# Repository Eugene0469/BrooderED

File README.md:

# BrooderED
This repo contains all ED of the brooder bora

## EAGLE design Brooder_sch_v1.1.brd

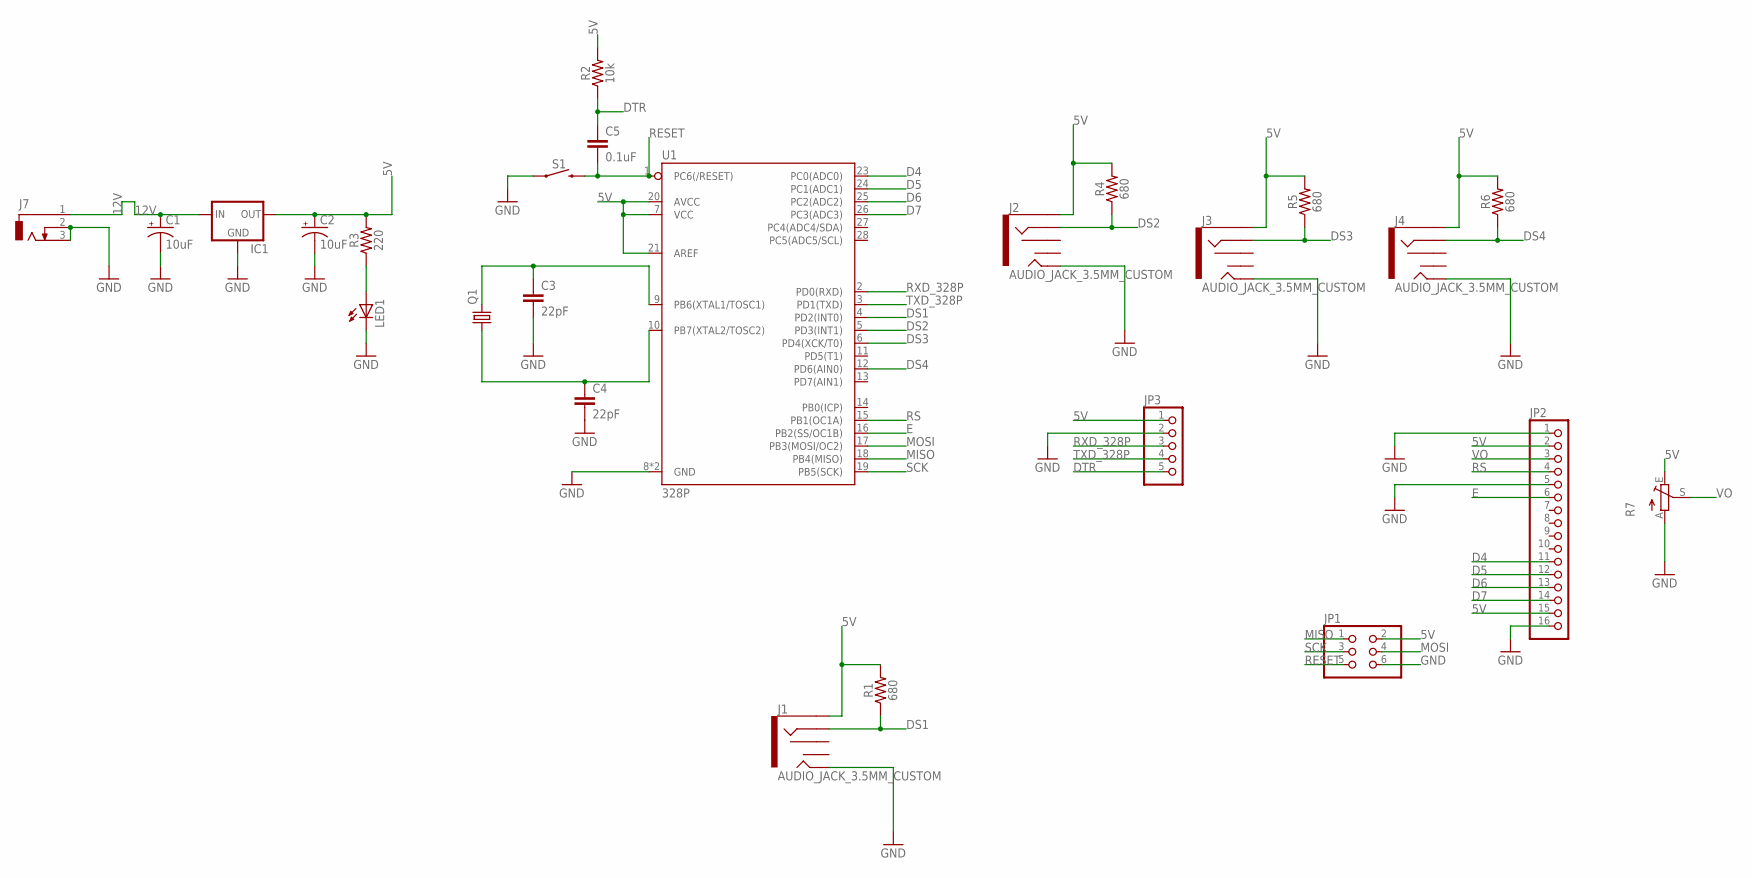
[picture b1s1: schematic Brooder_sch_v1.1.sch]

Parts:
C1, C2: 10uF; CPOL-RADIAL-2.5MM-5MM
C3, C4: 22pF; CAP-PTH-2.54
C5: 0.1uF; CAP-PTH-2.54
IC1: 78XXS
J1, J2, J3, J4: AUDIO_JACK_3.5MM_CUSTOM; AUDIO-JACK_CUSTOM
J7: DCJ0303_CUSTOM
JP1: PINHD-2X3; 2X03
JP2: PINHD-1X16; 1X16
JP3: PINHD-1X5; 1X05
LED1: LED5MM
Q1: CRYSTALHC49S; HC49/S
R1, R4, R5, R6: 680; AXIAL-0.3
R2: 10k; AXIAL-0.3
R3: 220; AXIAL-0.3
R7: TRIM_EU-CT6; CT6
S1: SWITCH; TACTILE_SWITCH_PTH_6.0MM
U1: 328P; DIP28

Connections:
5V: C2.1 (+), IC1.OUT, J1.SLEEVE, J2.SLEEVE, J3.SLEEVE, J4.SLEEVE, JP1.2, JP2.2, JP2.15, JP3.1, R1.P$2 (2), R2.P$2 (2), R3.P$2 (2), R4.P$2 (2), R5.P$2 (2), R6.P$2 (2), R7.E, U1.7 (VCC), U1.20 (AVCC), U1.21 (AREF)
12V: C1.1 (+), IC1.IN, J7.1
D4: JP2.11, U1.23 (PC0(ADC0))
D5: JP2.12, U1.24 (PC1(ADC1))
D6: JP2.13, U1.25 (PC2(ADC2))
D7: JP2.14, U1.26 (PC3(ADC3))
DS1: J1.RING, R1.P$1 (1), U1.4 (PD2(INT0))
DS2: J2.RING, R4.P$1 (1), U1.5 (PD3(INT1))
DS3: J3.RING, R5.P$1 (1), U1.6 (PD4(XCK/T0))
DS4: J4.RING, R6.P$1 (1), U1.12 (PD6(AIN0))
DTR: C5.1, JP3.5, R2.P$1 (1)
E: JP2.6, U1.16 (PB2(SS/OC1B))
GND: C1.2 (-), C2.2 (-), C3.2, C4.2, IC1.GND, J1.TIP, J2.TIP, J3.TIP, J4.TIP, J7.2, J7.3, JP1.6, JP2.1, JP2.5, JP2.16, JP3.2, LED1.K (C), R7.A, S1.1, U1.8 (GND), U1.22 (GND)
MISO: JP1.1, U1.18 (PB4(MISO))
MOSI: JP1.4, U1.17 (PB3(MOSI/OC2))
unnamed: LED1.A, R3.P$1 (1)
unnamed: C4.1, Q1.1, U1.10 (PB7(XTAL2/TOSC2))
unnamed: C3.1, Q1.2, U1.9 (PB6(XTAL1/TOSC1))
RESET: C5.2, JP1.5, S1.3 (2), U1.1 (PC6(/RESET))
RS: JP2.4, U1.15 (PB1(OC1A))
RXD_328P: JP3.3, U1.2 (PD0(RXD))
SCK: JP1.3, U1.19 (PB5(SCK))
TXD_328P: JP3.4, U1.3 (PD1(TXD))
VO: JP2.3, R7.S

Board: 2 copper layers, 25 parts (1 on the bottom side), 24 nets, no tracks yet.

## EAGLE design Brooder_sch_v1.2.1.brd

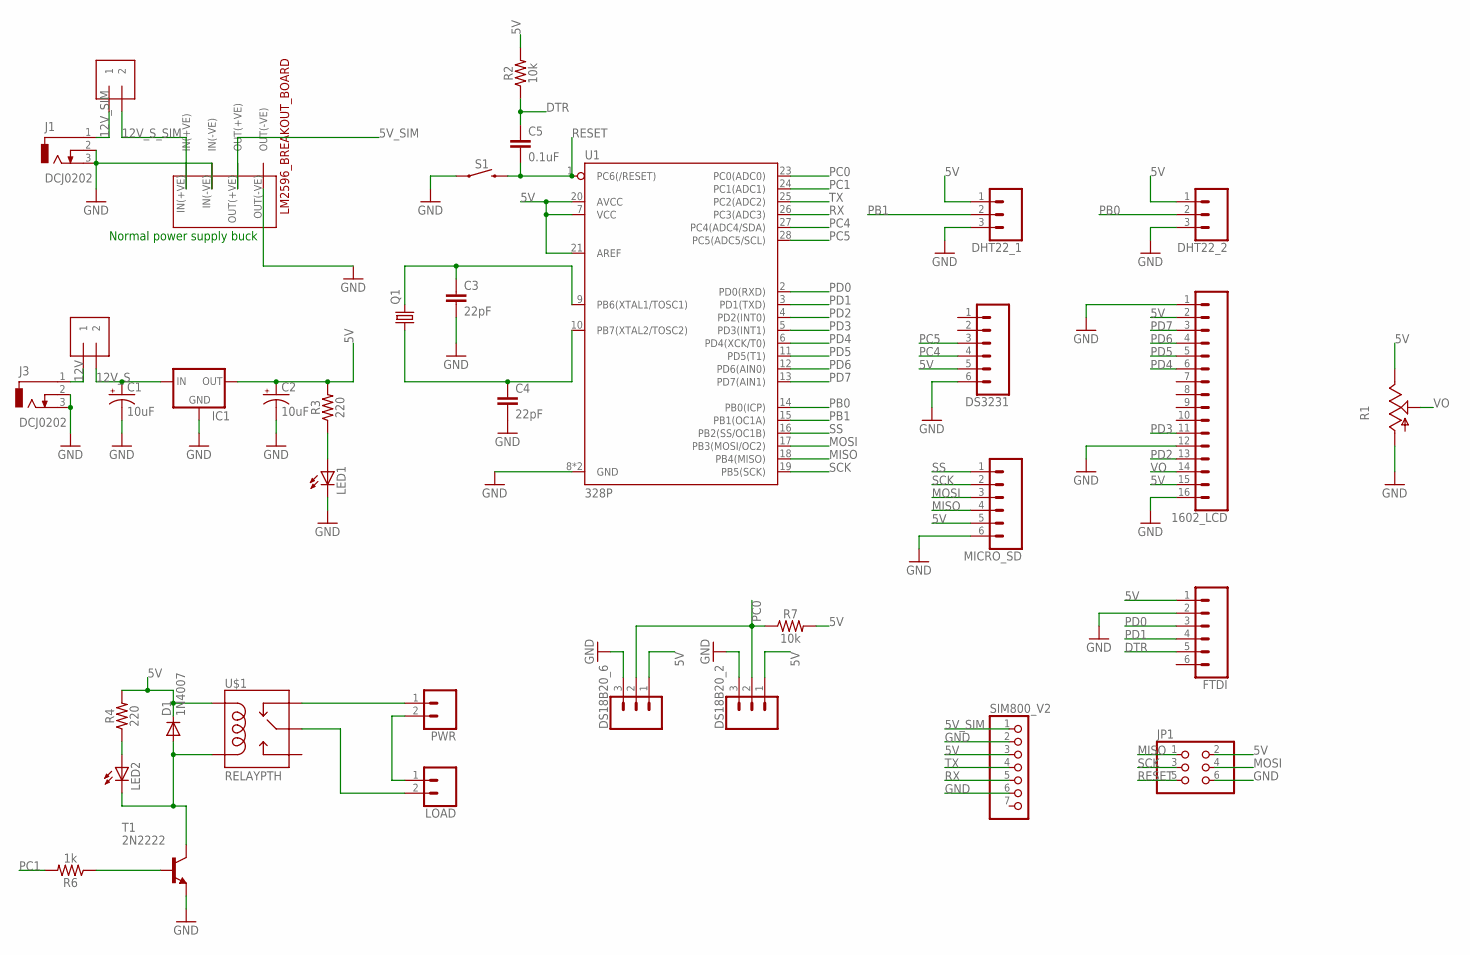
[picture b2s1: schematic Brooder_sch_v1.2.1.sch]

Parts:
1602_LCD: CONN_161X16_NO_SILK; 1X16_NO_SILK
C1, C2: 10uF; CPOL-RADIAL-2.5MM-5MM
C3, C4: 22pF; CAP-PTH-2.54
C5: 0.1uF; CAP-PTH-2.54
D1: 1N4007; DO41-10
DHT22_1: dht22_1; 1X03
DHT22_2: 455-1750-1-ND; 1X03
DS18B20_2, DS18B20_6: 455-1750-1-ND; 1X03
DS3231: CONN_06NO_SILK_FEMALE_PTH; 1X06_NO_SILK
FTDI: CONN_06NO_SILK_FEMALE_PTH; 1X06_NO_SILK
IC1: 78XXS
J1, J3: DCJ0202
J2, J4: 1X2-3.5MM
JP1: PINHD-2X3; 2X03
LED1, LED2: LED5MM
LOAD: CONN_025MM; SCREWTERMINAL-5MM-2
MICRO_SD: CONN_06NO_SILK_FEMALE_PTH; 1X06_NO_SILK
PWR: CONN_025MM; SCREWTERMINAL-5MM-2
Q1: CRYSTALHC49S; HC49/S
R1: TRIM_US-CT6; CT6
R2, R7: 10k; AXIAL-0.3
R3, R4: 220; AXIAL-0.3
R6: 1k; AXIAL-0.3
S1: SWITCH; TACTILE_SWITCH_PTH_6.0MM
SIM800_V2: PINHD-1X7; 1X07
T1: 2N2222; TO92-EBC-OVAL
U1: 328P; DIP28
U$1: RELAYPTH; SRD-05VDC-SL-C
U$2: LM2596_BREAKOUT_BOARDTHROUGH_HOLE; LM2596_BREAKOUTBOARD

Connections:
5V: 1602_LCD.2, 1602_LCD.15, C2.1 (+), D1.C, DHT22_1.1, DHT22_2.1, DS18B20_2.1, DS18B20_6.1, DS3231.5, FTDI.1, IC1.OUT, JP1.2, MICRO_SD.5, R1.E, R2.P$2 (2), R3.P$2 (2), R4.P$2 (2), R7.P$2 (2), SIM800_V2.3, U1.7 (VCC), U1.20 (AVCC), U1.21 (AREF), U$1.COIL1
5V_SIM: SIM800_V2.1, U$2.OUT(+VE)
12V: J3.1, J4.1
12V_S: C1.1 (+), IC1.IN, J4.2
12V_SIM: J1.1, J2.1
12V_S_SIM: J2.2, U$2.IN(+VE)
DTR: C5.1, FTDI.5, R2.P$1 (1)
GND: 1602_LCD.1, 1602_LCD.12, 1602_LCD.16, C1.2 (-), C2.2 (-), C3.2, C4.2, DHT22_1.3, DHT22_2.3, DS18B20_2.3, DS18B20_6.3, DS3231.6, FTDI.2, IC1.GND, J1.2, J1.3, J3.2, J3.3, JP1.6, LED1.K (C), MICRO_SD.6, R1.A, S1.1, SIM800_V2.2, SIM800_V2.6, T1.E, U1.8 (GND), U1.22 (GND), U$2.IN(-VE), U$2.OUT(-VE)
MISO: JP1.1, MICRO_SD.4, U1.18 (PB4(MISO))
MOSI: JP1.4, MICRO_SD.3, U1.17 (PB3(MOSI/OC2))
unnamed: LOAD.2, U$1.SWCOMMON
unnamed: LED1.A, R3.P$1 (1)
unnamed: LOAD.1, PWR.2
unnamed: C4.1, Q1.1, U1.10 (PB7(XTAL2/TOSC2))
unnamed: D1.A, LED2.K (C), T1.C, U$1.COIL0
unnamed: LED2.A, R4.P$1 (1)
unnamed: C3.1, Q1.2, U1.9 (PB6(XTAL1/TOSC1))
unnamed: R6.P$1 (1), T1.B
unnamed: PWR.1, U$1.SWCLOSED (SWCLOSE)
PB0: DHT22_2.2, U1.14 (PB0(ICP))
PB1: DHT22_1.2, U1.15 (PB1(OC1A))
PC0: DS18B20_2.2, DS18B20_6.2, R7.P$1 (1), U1.23 (PC0(ADC0))
PC1: R6.P$2 (2), U1.24 (PC1(ADC1))
PC4: DS3231.4, U1.27 (PC4(ADC4/SDA))
PC5: DS3231.3, U1.28 (PC5(ADC5/SCL))
PD0: FTDI.3, U1.2 (PD0(RXD))
PD1: FTDI.4, U1.3 (PD1(TXD))
PD2: 1602_LCD.13, U1.4 (PD2(INT0))
PD3: 1602_LCD.11, U1.5 (PD3(INT1))
PD4: 1602_LCD.6, U1.6 (PD4(XCK/T0))
PD5: 1602_LCD.5, U1.11 (PD5(T1))
PD6: 1602_LCD.4, U1.12 (PD6(AIN0))
PD7: 1602_LCD.3, U1.13 (PD7(AIN1))
RESET: C5.2, JP1.5, S1.3 (2), U1.1 (PC6(/RESET))
RX: SIM800_V2.5, U1.26 (PC3(ADC3))
SCK: JP1.3, MICRO_SD.2, U1.19 (PB5(SCK))
SS: MICRO_SD.1, U1.16 (PB2(SS/OC1B))
TX: SIM800_V2.4, U1.25 (PC2(ADC2))
VO: 1602_LCD.14, R1.S

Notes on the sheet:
Normal power supply buck

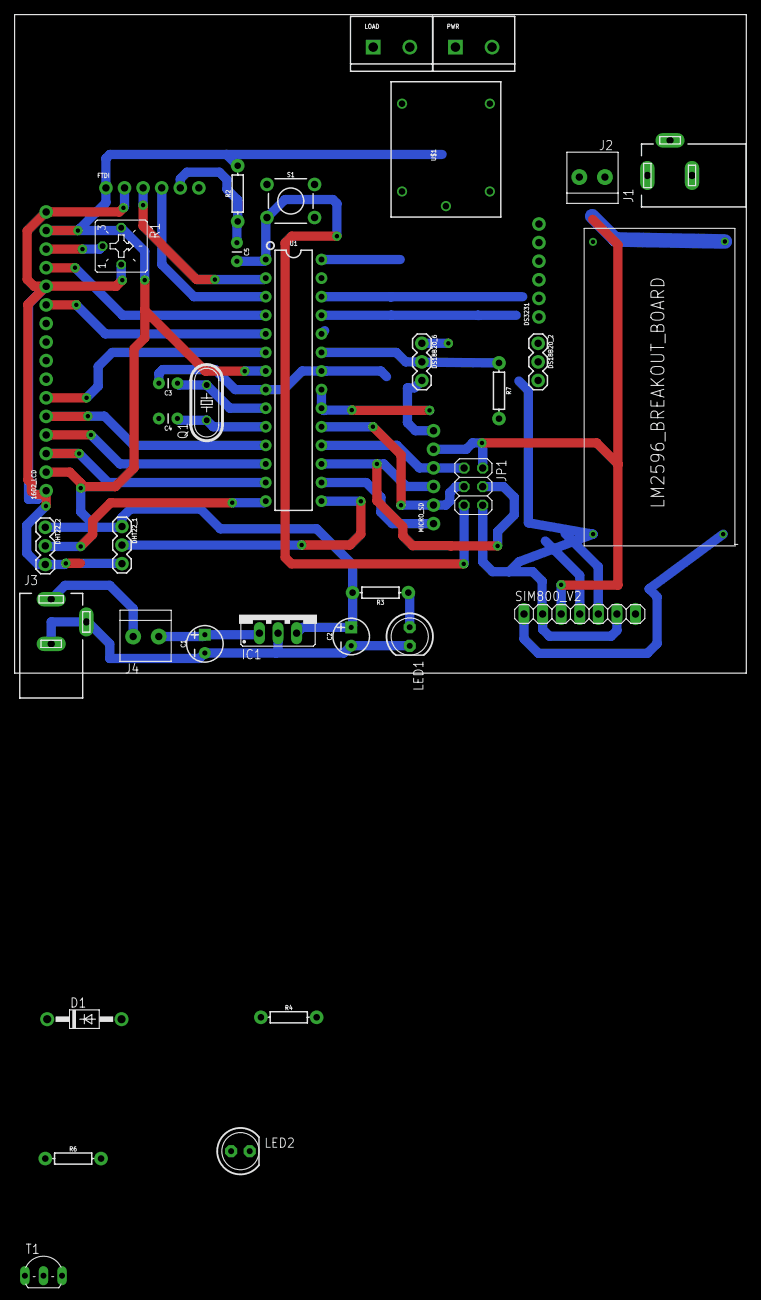
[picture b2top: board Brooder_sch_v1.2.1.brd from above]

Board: 2 copper layers, 100.0 x 90.0 mm, 37 parts (0 on the bottom side), 39 nets.

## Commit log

2019-09-19 Adds schematic design with 6 ds18b20, 2 dht, 1 lcd, 1 microSD and 1 FTDI
2019-09-19 Adds the PCB layout
2019-09-23 Changes the lcd positioning, moves the microSD and corrects the FTDI pin mapping
2019-09-23 Adds the top ground plane
2019-09-24 Adds BOM
2019-09-28 Modifies the potentiometer specifications in the BOM
2019-09-28 Adds space for the rocker switch
2019-09-28 Adds the RTC clock
2019-09-28 Adds test led
2019-09-28 Adds actual pot symbol
2019-09-28 Resolves inconsistencies between the board and schematic
2019-09-28 Completes redesign of the board
2019-09-28 Joins the bottom ground plane into one
2019-10-07 Replaces the 7805 eith the lm2596 buck converter
2019-10-07 Removes four of the six ds18b20 sensor connector
2019-10-07 Removes the dht22 resistors
2019-10-07 Adds the sim800l V2 pin headers
2019-10-07 Adds the sim800 to the PCB board
2019-10-10 Adds separate power source for sim800l and board
2019-10-14 Increases gms power supply track from 1.27mm to 2mm
2019-10-16 Replaces pot rj6 with pot ct6
2019-10-21 Links lcd and dht grounds
2019-10-21 Adds ICSP header
2019-10-21 Switches orientation of the sim800l
2019-10-21 Adds untracked ICSP header
2019-10-27 Adds extractor fan relay to schematic
2019-10-27 Removes test led fro schematic
2019-10-27 Adds extra terminal block to the relay
2019-10-27 Increases the size of the board from 90*75mm to 100*90mm
2019-10-27 Replaces ds3231 header pins with ds3231 symbol
2019-10-27 Adds new file due to file locking
2019-10-27 Replaces both power jacks with header pins
2019-10-28 Adds custom sim800V2 library symbol to schematic
2019-10-28 Adds custom sd card module library symbol to schematic
2019-10-28 Adds i2c header pin in place of lcd pins and potentiometer
2019-10-28 Replace ds3231 library symbol with 10 pins with that that has 4 pins
2019-11-07 Removes extra ds18b20 pin
2019-11-07 Adds resitor to dht22(680)
2019-11-07 Switches the signal and ground signals for all the sensors
2019-11-07 Adds allocation for water flow sensor
2019-11-07 Replaces sim800l v2 with sim800l v1
2019-11-13 Adds sim800 reset pin
2019-12-19 Initial Commit for the Basic board
2019-12-19 Deletes unused components
2019-12-19 Replaces sensor ports with audio jacks
2019-12-19 Replaces 12c for lcd with 16 header pin
2019-12-19 Places the component to the board
2019-12-19 Completes basic pcb board
2019-12-19 Create Brooder_sch_v1.1.b##
2019-12-19 Replaces 6pin FTDI header with a 5 pin one

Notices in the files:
parts and their libraries:
SparkFun-Connectors: Licensing: Creative Commons ShareAlike 4.0 International - https://creativecommons.org/licenses/by-sa/4.0
